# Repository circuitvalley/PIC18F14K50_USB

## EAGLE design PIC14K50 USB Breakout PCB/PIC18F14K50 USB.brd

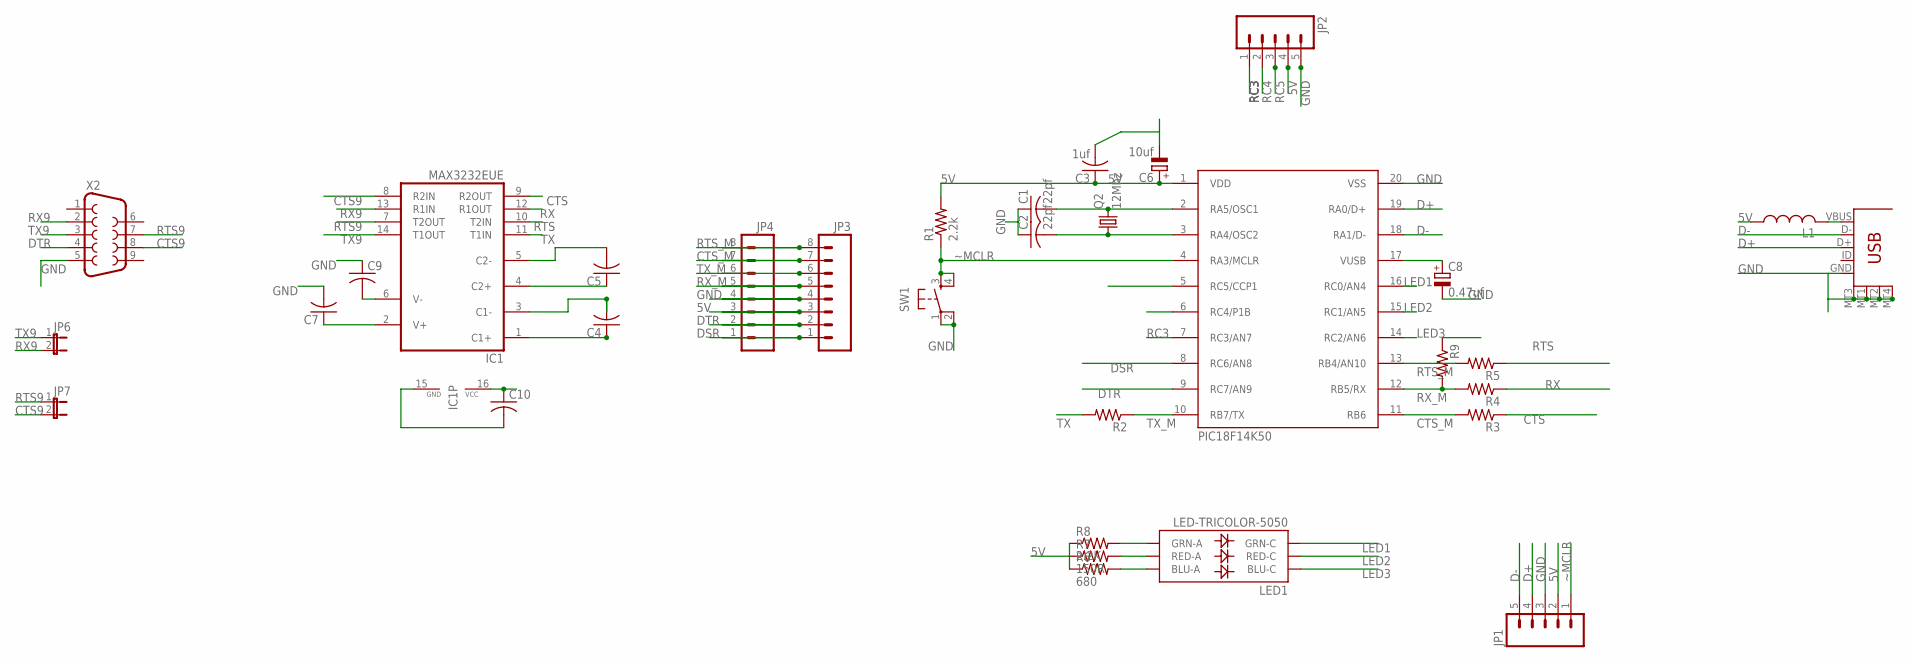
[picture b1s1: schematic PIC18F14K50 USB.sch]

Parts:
C1, C2: 22pf; C0805
C3: 1uf; C0805
C4, C5, C7, C9, C10: C-USC0805; C0805
C6: 10uf; SMC_B
C8: 0.47uf; SMC_B
IC1: MAX3232EUE; TSSOP16
JP1, JP2: M05PTH; 1X05
JP3, JP4: M081X08; 1X08
JP6, JP7: JUMPER-2PTH; 1X02
L1: L-USL3225M; L3225M
LED1: LED-TRICOLOR-5050
PIC18F14K50: PIC18F14K50D; SSOP20
Q2: 12Mhz; HC49UP
R1: 2.2k; M0805
R2, R3, R4, R5, R9: R-US_M0805; M0805
R6: 680; M0805
R7: 150R; M0805
R8: 2.2K; M0805
SW1: SW-SMD-SMALL; TACT_SWITCH_SMALL
U$1: USB-MICROB-HW-MC-5F; USB-MICROB-HW-MC-5F-01
X2: F09D

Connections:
5V: C3.1, C6.+, C10.1, IC1.16 (VCC), JP1.2, JP2.4, JP3.3, JP4.3, L1.1, PIC18F14K50.1 (VDD), R1.2, R6.1, R7.1, R8.1, R9.1; also elsewhere on the board
CTS: IC1.9 (R2OUT), R3.1
CTS9: IC1.8 (R2IN), JP7.2, X2.8
CTS_M: JP3.7, JP4.7, PIC18F14K50.11 (RB6), R3.2; also elsewhere on the board
D+: JP1.4, PIC18F14K50.19 (RA0/D+), U$1.D+; also elsewhere on the board
D-: JP1.5, PIC18F14K50.18 (RA1/D-), U$1.D-; also elsewhere on the board
DSR: JP3.1, JP4.1, PIC18F14K50.8 (RC6/AN8); also elsewhere on the board
DTR: JP3.2, JP4.2, PIC18F14K50.9 (RC7/AN9), X2.4; also elsewhere on the board
GND: C1.1, C2.1, C3.2, C6.-, C7.2, C8.-, C9.1, C10.2, IC1.15 (GND), JP1.3, JP2.5, JP3.4, JP4.4, PIC18F14K50.20 (VSS), SW1.1, SW1.2, U$1.GND, U$1.MT1 (MTN3), U$1.MT2 (MTN4), U$1.MT3 (MTN1), U$1.MT4 (MTN2), X2.5; also elsewhere on the board
LED1: LED1.3 (GRN-C), PIC18F14K50.16 (RC0/AN4); also elsewhere on the board
LED2: LED1.2 (RED-C), PIC18F14K50.15 (RC1/AN5); also elsewhere on the board
LED3: LED1.1 (BLU-C), PIC18F14K50.14 (RC2/AN6); also elsewhere on the board
unnamed 12: C2.2, PIC18F14K50.3 (RA4/OSC2), Q2.1; also elsewhere on the board
unnamed 13: C1.2, PIC18F14K50.2 (RA5/OSC1), Q2.2; also elsewhere on the board
unnamed 14: JP2.3, PIC18F14K50.5 (RC5/CCP1); also elsewhere on the board
unnamed 15: JP2.2, PIC18F14K50.6 (RC4/P1B); also elsewhere on the board
unnamed 16: JP2.1, PIC18F14K50.7 (RC3/AN7); also elsewhere on the board
unnamed: LED1.6 (BLU-A), R6.2
unnamed: LED1.5 (RED-A), R7.2
unnamed: LED1.4 (GRN-A), R8.2
unnamed: C4.1, IC1.1 (C1+)
unnamed: C4.2, IC1.3 (C1-)
unnamed: C5.1, IC1.4 (C2+)
unnamed: C5.2, IC1.5 (C2-)
unnamed: C7.1, IC1.2 (V+)
unnamed: C9.2, IC1.6 (V-)
unnamed 34: C8.+, PIC18F14K50.17 (VUSB); also elsewhere on the board
RTS: IC1.10 (T2IN), R5.1
RTS9: IC1.7 (T2OUT), JP7.1, X2.7
RTS_M: JP3.8, JP4.8, PIC18F14K50.13 (RB4/AN10), R5.2; also elsewhere on the board
RX: IC1.12 (R1OUT), R4.1
RX9: IC1.13 (R1IN), JP6.2, X2.2
RX_M: JP3.5, JP4.5, PIC18F14K50.12 (RB5/RX), R4.2, R9.2; also elsewhere on the board
TX: IC1.11 (T1IN), R2.2
TX9: IC1.14 (T1OUT), JP6.1, X2.3
TX_M: JP3.6, JP4.6, PIC18F14K50.10 (RB7/TX), R2.1; also elsewhere on the board
VBUS5V: L1.2, U$1.VBUS
~MCLR: JP1.1, PIC18F14K50.4 (RA3/MCLR), R1.1, SW1.3, SW1.4; also elsewhere on the board

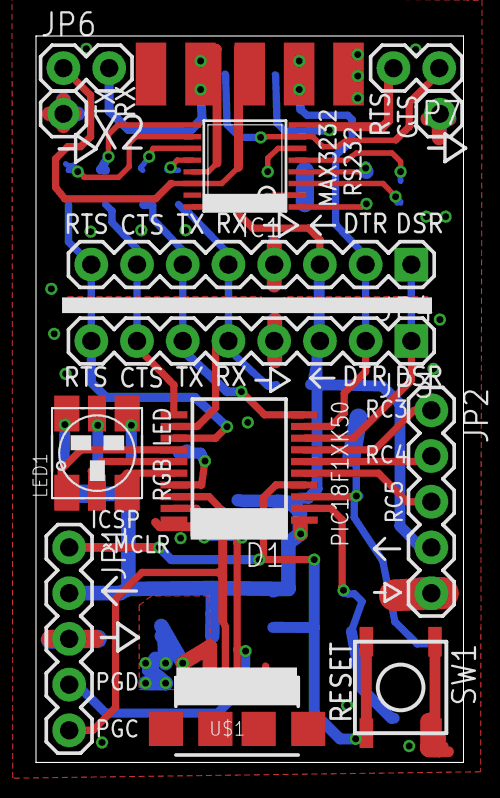
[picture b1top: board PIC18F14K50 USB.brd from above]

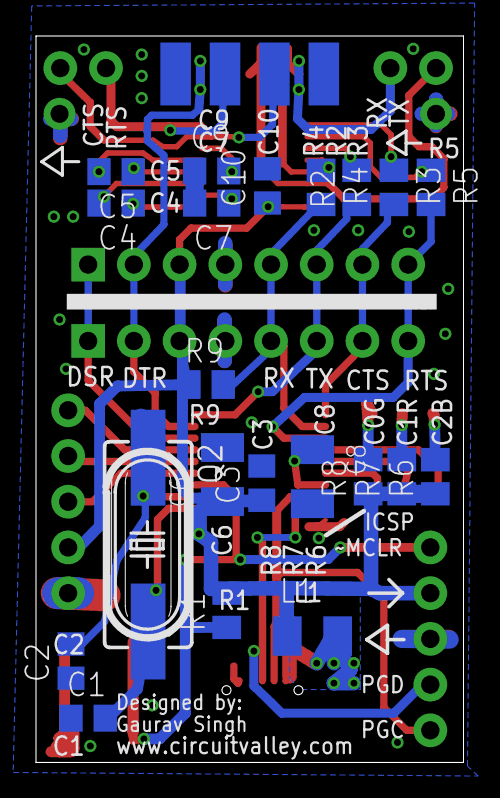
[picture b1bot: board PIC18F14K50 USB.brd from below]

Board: 2 copper layers, 23.8 x 40.4 mm, 33 parts (21 on the bottom side), 38 nets.

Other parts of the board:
D1: PIC18F14K50D; SSOP20

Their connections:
5V: D1.1; also elsewhere on the board
CTS_M: D1.11; also elsewhere on the board
D+: D1.19; also elsewhere on the board
D-: D1.18; also elsewhere on the board
DSR: D1.8; also elsewhere on the board
DTR: D1.9; also elsewhere on the board
GND: D1.20; also elsewhere on the board
LED1: D1.16; also elsewhere on the board
LED2: D1.15; also elsewhere on the board
LED3: D1.14; also elsewhere on the board
unnamed 12: D1.3; also elsewhere on the board
unnamed 13: D1.2; also elsewhere on the board
unnamed 14: D1.5; also elsewhere on the board
unnamed 15: D1.6; also elsewhere on the board
unnamed 16: D1.7; also elsewhere on the board
unnamed 34: D1.17; also elsewhere on the board
RTS_M: D1.13; also elsewhere on the board
RX_M: D1.12; also elsewhere on the board
TX_M: D1.10; also elsewhere on the board
~MCLR: D1.4; also elsewhere on the board

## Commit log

2015-01-23 pcb files added
2015-01-23 silk fix

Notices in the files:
parts and their libraries:
SparkFun: Licensing: CC v3.0 Share-Alike You are welcome to use this library for commercial purposes.
